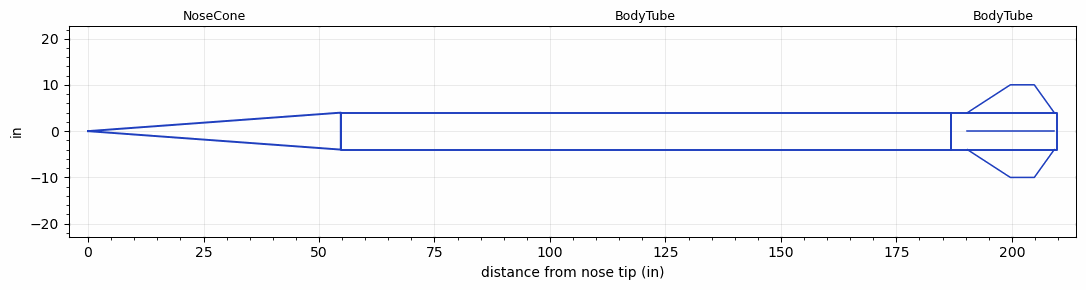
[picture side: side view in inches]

<RASAeroDocument>
 <FileVersion>2</FileVersion>
 <RocketDesign>
  <NoseCone>
   <Length>54.7243</Length>
   <Diameter>8</Diameter>
   <Shape>Conical</Shape>
   <Location>0</Location>
  </NoseCone>
  <BodyTube>
   <Length>131.9997</Length>
   <Diameter>8</Diameter>
   <Location>54.7243</Location>
  </BodyTube>
  <BodyTube>
   <Length>23</Length>
   <Diameter>8</Diameter>
   <Location>186.724</Location>
   <Fin>
    <Count>4</Count>
    <Chord>18.7962</Chord>
    <Span>6.0236</Span>
    <SweepDistance>9.2913</SweepDistance>
    <TipChord>5.1898</TipChord>
    <Thickness>0.25</Thickness>
    <Location>19.3474</Location>
    <AirfoilSection>Square</AirfoilSection>
   </Fin>
  </BodyTube>
  <Surface>Rough Camouflage Paint</Surface>
  <CD>0</CD>
  <ModifiedBarrowman>False</ModifiedBarrowman>
  <Turbulence>False</Turbulence>
  <UseBooster1>False</UseBooster1>
  <UseBooster2>False</UseBooster2>
  <Comments>Testing for stability --&gt; upthrust sim</Comments>
 </RocketDesign>
 <LaunchSite>
  <Altitude>0</Altitude>
  <Pressure>29.9214</Pressure>
  <RodAngle>0</RodAngle>
  <RodLength>3.2808</RodLength>
  <Temperature>59</Temperature>
  <WindSpeed>4.4739</WindSpeed>
 </LaunchSite>
 <Recovery>
  <Altitude1>0</Altitude1>
  <Altitude2>0</Altitude2>
  <DeviceType1>None</DeviceType1>
  <DeviceType2>None</DeviceType2>
  <Event1>False</Event1>
  <Event2>False</Event2>
  <Size1>0</Size1>
  <Size2>0</Size2>
  <EventType1>None</EventType1>
  <EventType2>None</EventType2>
  <CD1>0</CD1>
  <CD2>0</CD2>
 </Recovery>
 <SimulationList>
  <Simulation>
   <SustainerLaunchWt>110.4736</SustainerLaunchWt>
   <SustainerCG>131.7774</SustainerCG>
   <SustainerIgnitionDelay>0</SustainerIgnitionDelay>
   <Booster1SeparationDelay>0</Booster1SeparationDelay>
   <Booster1IgnitionDelay>0</Booster1IgnitionDelay>
   <IncludeBooster1>False</IncludeBooster1>
   <Booster2Delay>0</Booster2Delay>
   <IncludeBooster2>False</IncludeBooster2>
  </Simulation>
 </SimulationList>
</RASAeroDocument>
